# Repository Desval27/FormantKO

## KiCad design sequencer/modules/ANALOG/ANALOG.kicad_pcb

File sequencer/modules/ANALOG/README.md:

# ANALOG

Format: Single Height 160mm x 100mm

## Status

⚠️ Incomplete⚠️

## Documents

- [Schematic](plots/ANALOG__schematic.pdf)
<!--
- [Assembly](plots/CLOCK__Assembly.pdf)
- [Interactive Bill of Materials](bom/ibom.html)
-->

## Gerber to Order

⚠️ Untested⚠️

## Images

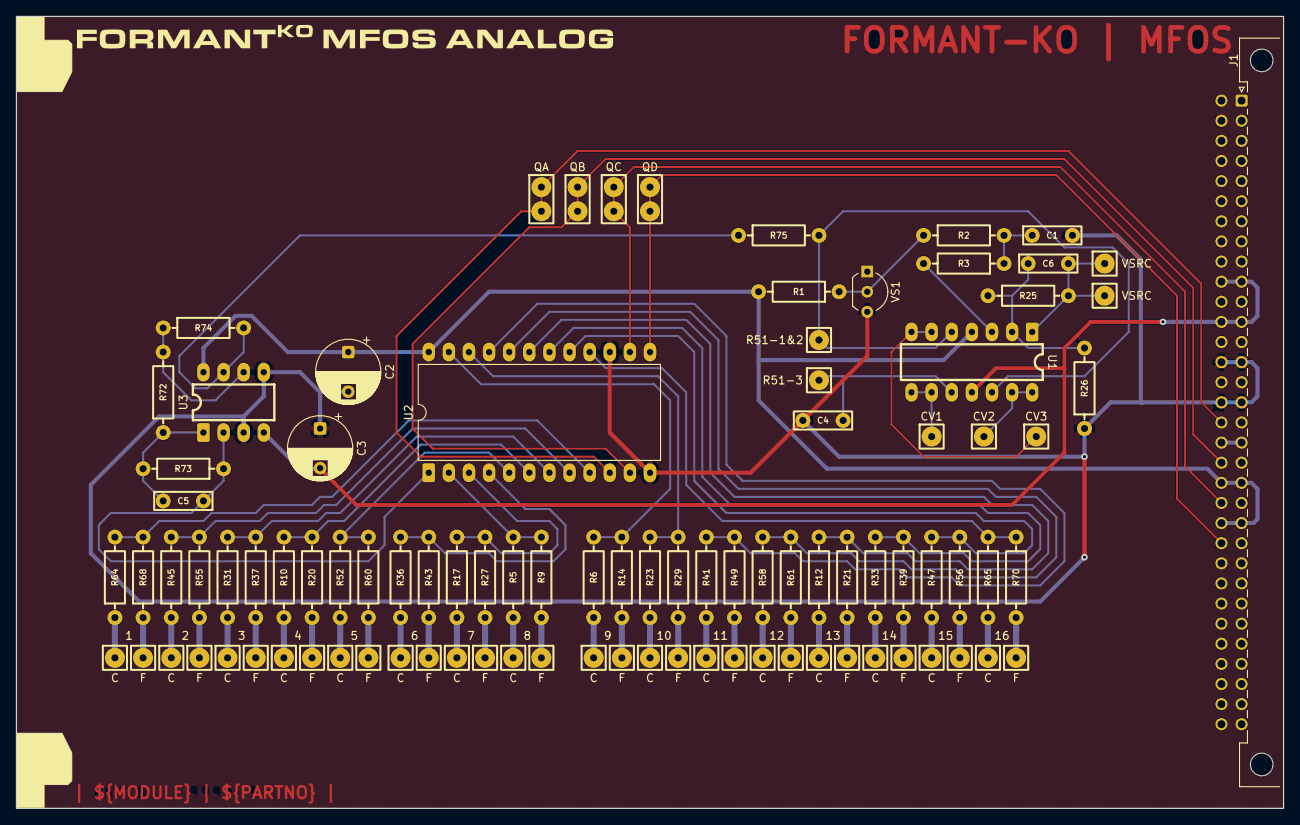
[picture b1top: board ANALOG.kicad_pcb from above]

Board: 2 copper layers, 160.0 x 100.0 mm, 96 parts (0 on the bottom side), 70 nets.

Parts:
C1, C4: 100n; C_Rect_200
C2, C3: 100µ; CP_Radial_D8.0mm_P5.00mm
C5, C6: 470p; C_Rect_200
J1: Sequencer Bus Connector; BusConnector_Full_Male_Horizontal
J2: QA; Wire_2x01_General
J3: QB; Wire_2x01_General
J4: QC; Wire_2x01_General
J5: QD; Wire_2x01_General
J6: CV1; Wire_1x01_General
J7: CV2; Wire_1x01_General
J8: CV3; Wire_1x01_General
J9: R51-1&2; Wire_1x01_General
J10: R51-3; Wire_1x01_General
J11, J12: VSRC; Wire_1x01_General
J13, J15, J17, J19, J21, J23, J25, J27, J29, J31, J33, J35, J37, J39, J41, J43: C; Wire_1x01_General
J14, J16, J18, J20, J22, J24, J26, J28, J30, J32, J34, J36, J38, J40, J42, J44: F; Wire_1x01_General
MH1: CardBracket
R1, R72, R74: 10k; R_Axial_Horizontal_400
R2, R3: 47k; R_Axial_Horizontal_400
R5, R6, R10, R12, R17, R23, R26, R31, R33, R36, R41, R45, R47, R52, R58, R64, R65, R73: 100k; R_Axial_Horizontal_400
R9, R14, R20, R21, R27, R29, R37, R39, R43, R49, R55, R56, R60, R61, R68, R70: 2M; R_Axial_Horizontal_400
R25: 200k; R_Axial_Horizontal_400
R75: 22R; R_Axial_Horizontal_400
U1: TL084; DIP-14
U2: CD4067; DIP-24W
U3: TL082; DIP-8
VS1: LM4040LP-2.5; TO-92_Inline_Wide

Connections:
+5V: J1.a18 (+5V), J1.b18 (+5V)
+15V: C2.1, J1.a20 (+15V), J1.a22 (+15V), J1.b20 (+15V), J1.b22 (+15V), R1.2, U1.4 (V+), U2.24 (VDD), U3.8 (V+)
-15V: C3.2, J1.a10 (-15V), J1.a12 (-15V), J1.b10 (-15V), J1.b12 (-15V), U1.11 (V-), U3.4 (V-)
C0: J13.1 (Pin_1_1), R64.1
C1: J15.1 (Pin_1_1), R45.1
C2: J17.1 (Pin_1_1), R31.1
C3: J19.1 (Pin_1_1), R10.1
C4: J21.1 (Pin_1_1), R52.1
C5: J23.1 (Pin_1_1), R36.1
C6: J25.1 (Pin_1_1), R17.1
C7: J27.1 (Pin_1_1), R5.1
C8: J29.1 (Pin_1_1), R6.1
C9: J31.1 (Pin_1_1), R23.1
C10: J33.1 (Pin_1_1), R41.1
C11: J35.1 (Pin_1_1), R58.1
C12: J37.1 (Pin_1_1), R12.1
C13: J39.1 (Pin_1_1), R33.1
C14: J41.1 (Pin_1_1), R47.1
C15: J43.1 (Pin_1_1), R65.1
CH0: R64.2, R68.2, U2.9 (Y0)
CH1: R45.2, R55.2, U2.8 (Y1)
CH2: R31.2, R37.2, U2.7 (Y2)
CH3: R10.2, R20.2, U2.6 (Y3)
CH4: R52.2, R60.2, U2.5 (Y4)
CH5: R36.2, R43.2, U2.4 (Y5)
CH6: R17.2, R27.2, U2.3 (Y6)
CH7: R5.2, R9.2, U2.2 (Y7)
CH8: R6.2, R14.2, U2.23 (Y8)
CH9: R23.2, R29.2, U2.22 (Y9)
CH10: R41.2, R49.2, U2.21 (Y10)
CH11: R58.2, R61.2, U2.20 (Y11)
CH12: R12.2, R21.2, U2.19 (Y12)
CH13: R33.2, R39.2, U2.18 (Y13)
CH14: R47.2, R56.2, U2.17 (Y14)
CH15: R65.2, R70.2, U2.16 (Y15)
CV: C5.1, R73.1, U2.1 (Z), U3.2 (-)
CV1: J6.1 (Pin_1_1), U1.8, U1.9 (-)
CV2: J7.1 (Pin_1_1), U1.13 (-), U1.14
CV3: J8.1 (Pin_1_1), U1.6 (-), U1.7
F0: J14.1 (Pin_1_1), R68.1
F1: J16.1 (Pin_1_1), R55.1
F2: J18.1 (Pin_1_1), R37.1
F3: J20.1 (Pin_1_1), R20.1
F4: J22.1 (Pin_1_1), R60.1
F5: J24.1 (Pin_1_1), R43.1
F6: J26.1 (Pin_1_1), R27.1
F7: J28.1 (Pin_1_1), R9.1
F8: J30.1 (Pin_1_1), R14.1
F9: J32.1 (Pin_1_1), R29.1
F10: J34.1 (Pin_1_1), R49.1
F11: J36.1 (Pin_1_1), R61.1
F12: J38.1 (Pin_1_1), R21.1
F13: J40.1 (Pin_1_1), R39.1
F14: J42.1 (Pin_1_1), R56.1
F15: J44.1 (Pin_1_1), R70.1
GND: C1.2, C2.2, C3.1, C4.2, J1.a14 (GND), J1.a16 (GND), J1.b14 (GND), J1.b16 (GND), R26.1, U2.12 (VSS), U2.15 (~E), U3.3 (+), U3.5 (+), VS1.3 (A)
unnamed: C1.1, R2.2, R3.1
unnamed: C5.2, R72.1, R73.2, U3.1
unnamed: R74.2, R75.1, U3.7
unnamed: R3.2, U1.3 (+)
unnamed: C6.1, R25.1, R26.2, U1.2 (-)
unnamed: R72.2, R74.1, U3.6 (-)
unnamed: R1.1, R2.1, VS1.2 (K)
QA: J1.b17 (A0), J2.1 (Pin_1_1), U2.10 (A0)
QB: J1.b19 (A1), J3.1 (Pin_1_1), U2.11 (A1)
QC: J1.b21 (A2), J4.1 (Pin_1_1), U2.14 (A2)
QD: J1.b23 (A3), J5.1 (Pin_1_1), U2.13 (A3)
R51-1&2: J9.1 (Pin_1_1), R75.2, U1.5 (+), U1.12 (+)
R51-3: C4.1, J10.1 (Pin_1_1), U1.10 (+)
VSRC: C6.2, J11.1 (Pin_1_1), J12.1 (Pin_1_1), R25.2, U1.1
